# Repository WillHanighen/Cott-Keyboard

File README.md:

# Cott Keyboard
## A shitty 14-key MIDI keyboard

Idiot attempts PCB design n stuff for first time

## Hardware
 - [ESP32-S3-DevKitC-1-N32R16V](https://www.aliexpress.us/item/3256803793464226.html?gatewayAdapt=glo2usa) (note: URL dose not auto-select proper variant)
 - [Adafruit Monochrome 1.12" 128x128 OLED](https://www.adafruit.com/product/5297)
 - [STEMMA QT / Qwiic JST SH 4-Pin Cable](https://www.adafruit.com/product/4399)
 - [Analog 2-axis Thumb Joystick with Select Button + Breakout Board](https://www.adafruit.com/product/512)
 - [NeoPixel 5050 RGB LED with Integrated Driver Chip](https://www.adafruit.com/product/1655) (10 pack, buy 2; 14 total required)

### Power notice

This project was designed arround being powered by the DevKit's USB-C port, and the USB spec is max. 900mA for USB3, and 500mA for USB2 (what the type-c port communicates as)
In other words, keep the LED brightness down (~25% max, stinky I know, take it up with the USB implments fourm for not making it 2A, as [power that be] intended) and avoid whites.

## License

Licensed under CC BY-NC-SA 4.0: You can freely edit and redistribute this project as long as you credit me, don't do it commercially, and/or for monetary gain, and publish it under the same license.

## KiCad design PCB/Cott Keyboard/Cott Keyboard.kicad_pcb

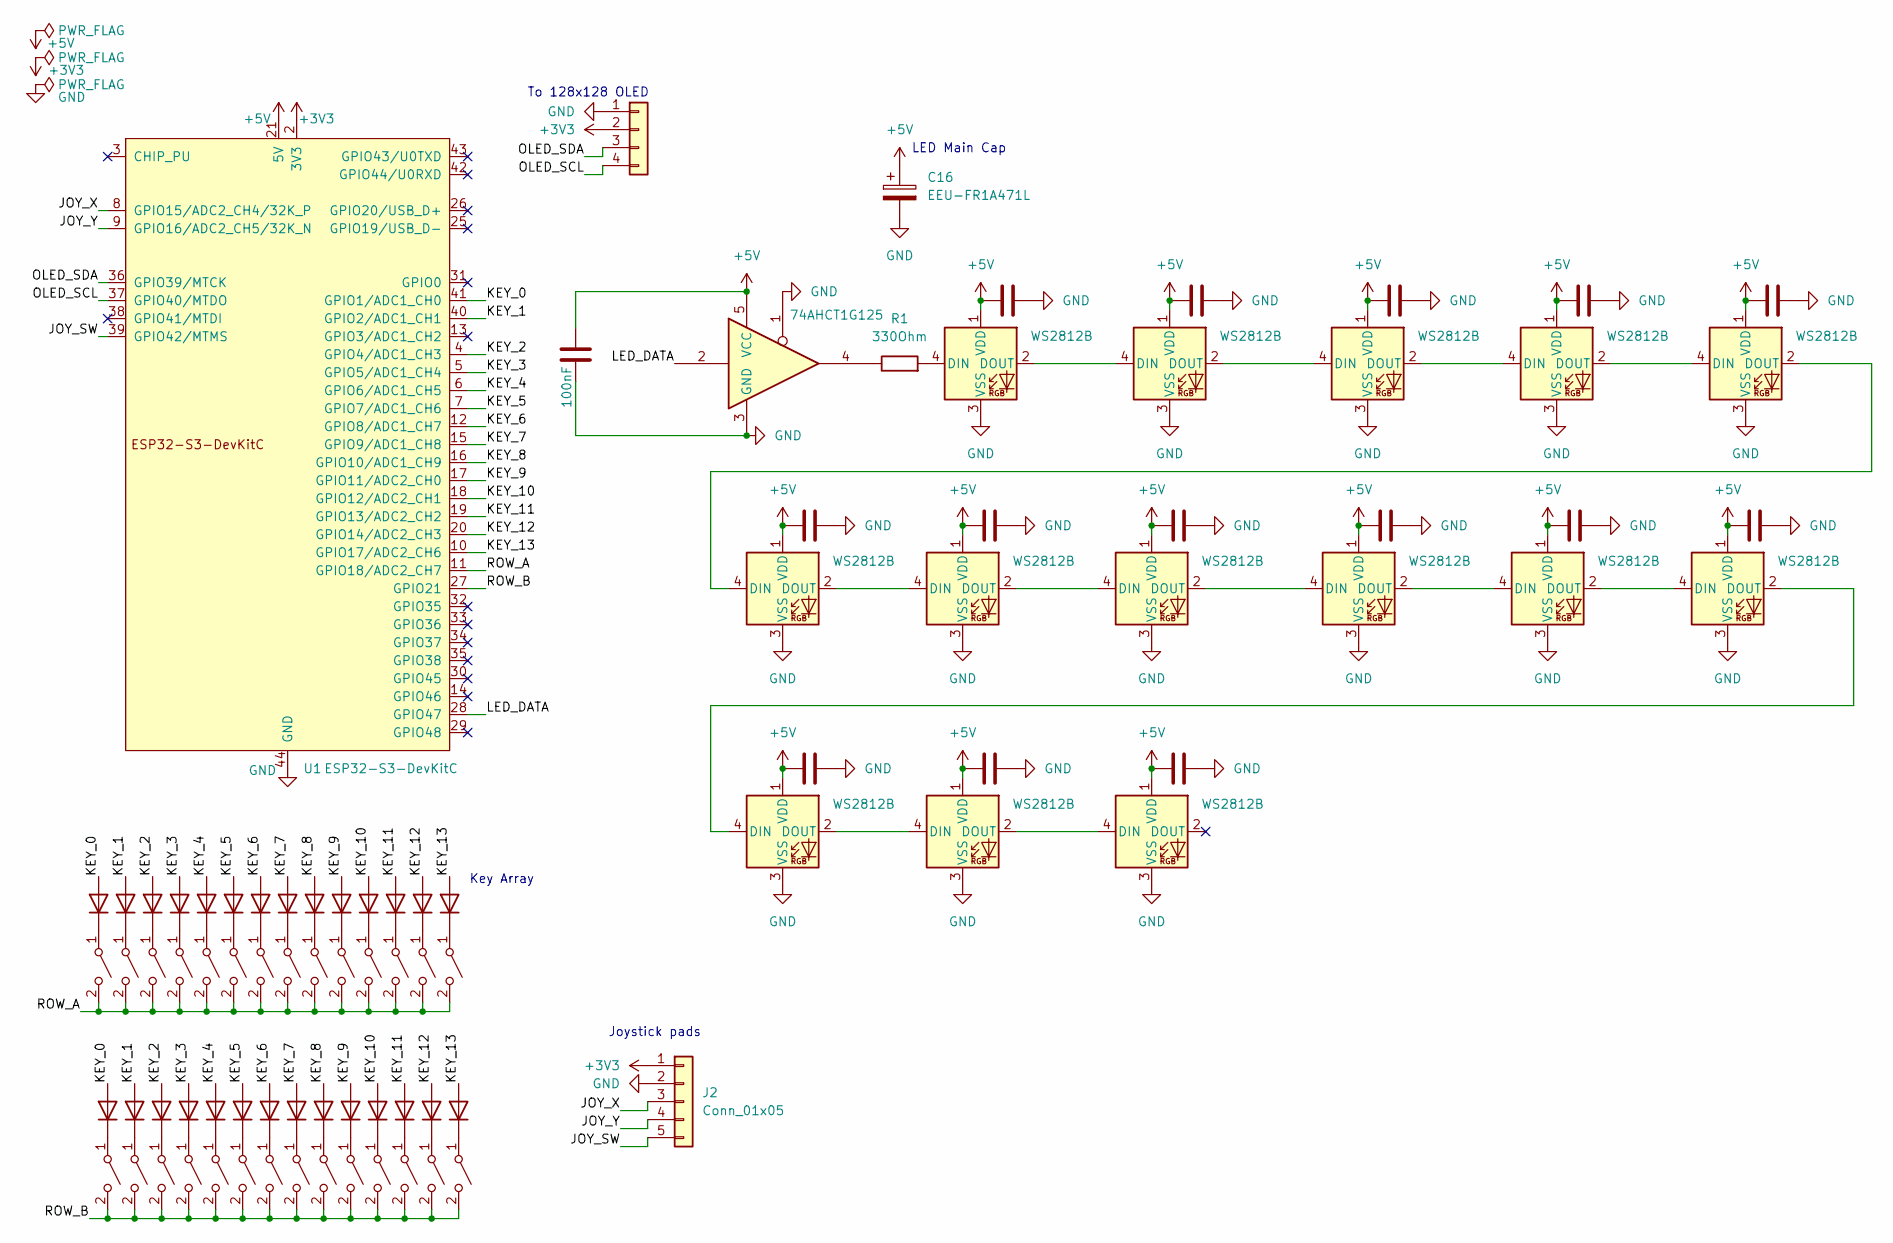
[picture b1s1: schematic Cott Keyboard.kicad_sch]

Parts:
C1, C2, C3, C4, C5, C6, C7, C8, C9, C10, C11, C12, C13, C14, C15: 100nF; C_0805_2012Metric_Pad1.18x1.45mm_HandSolder
C16: EEU-FR1A471L; CP_Radial_D8.0mm_P3.50mm
D1, D2, D3, D4, D5, D6, D7, D8, D9, D10, D11, D12, D13, D14, D15, D16, D17, D18, D19, D20, D21, D22, D23, D24, D25, D26, D27, D28: 1N4148W; D_SOD-123
D29, D30, D31, D32, D33, D34, D35, D36, D37, D38, D39, D40, D41, D42: WS2812B; LED_WS2812B_PLCC4_5.0x5.0mm_P3.2mm
J1: Conn_01x04; JST_SH_SM04B-SRSS-TB_1x04-1MP_P1.00mm_Horizontal
J2: Conn_01x05; SolderWire-0.25sqmm_1x05_P4.2mm_D0.65mm_OD1.7mm_Relief
R1: 330Ohm; R_0805_2012Metric_Pad1.20x1.40mm_HandSolder
SW1, SW2, SW3, SW4, SW5, SW6, SW7, SW8, SW9, SW10, SW11, SW12, SW13, SW14, SW15, SW16, SW17, SW18, SW19, SW20, SW21, SW22, SW23, SW24, SW25, SW26, SW27, SW28: D2F-01FL; SW_Omron_D2F-01FL_SPST_NO
U1: ESP32-S3-DevKitC
U2: 74AHCT1G125; SOT-23-5

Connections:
+3V3: J1.2, J2.1, U1.1 (3V3), U1.2 (3V3)
+5V: C1.1, C2.1, C3.1, C4.1, C5.1, C6.1, C7.1, C8.1, C9.1, C10.1, C11.1, C12.1, C13.1, C14.1, C15.2, C16.1, D29.1 (VDD), D30.1 (VDD), D31.1 (VDD), D32.1 (VDD), D33.1 (VDD), D34.1 (VDD), D35.1 (VDD), D36.1 (VDD), D37.1 (VDD), D38.1 (VDD), D39.1 (VDD), D40.1 (VDD), D41.1 (VDD), D42.1 (VDD), U1.21 (5V), U2.5 (VCC)
/JOY_SW: J2.5, U1.39 (GPIO42/MTMS)
/JOY_X: J2.3, U1.8 (GPIO15/ADC2_CH4/32K_P)
/JOY_Y: J2.4, U1.9 (GPIO16/ADC2_CH5/32K_N)
/KEY_0: D1.2 (A), D15.2 (A), U1.41 (GPIO1/ADC1_CH0)
/KEY_1: D2.2 (A), D16.2 (A), U1.40 (GPIO2/ADC1_CH1)
/KEY_2: D3.2 (A), D17.2 (A), U1.4 (GPIO4/ADC1_CH3)
/KEY_3: D4.2 (A), D18.2 (A), U1.5 (GPIO5/ADC1_CH4)
/KEY_4: D5.2 (A), D19.2 (A), U1.6 (GPIO6/ADC1_CH5)
/KEY_5: D6.2 (A), D20.2 (A), U1.7 (GPIO7/ADC1_CH6)
/KEY_6: D7.2 (A), D21.2 (A), U1.12 (GPIO8/ADC1_CH7)
/KEY_7: D8.2 (A), D22.2 (A), U1.15 (GPIO9/ADC1_CH8)
/KEY_8: D9.2 (A), D23.2 (A), U1.16 (GPIO10/ADC1_CH9)
/KEY_9: D10.2 (A), D24.2 (A), U1.17 (GPIO11/ADC2_CH0)
/KEY_10: D11.2 (A), D25.2 (A), U1.18 (GPIO12/ADC2_CH1)
/KEY_11: D12.2 (A), D26.2 (A), U1.19 (GPIO13/ADC2_CH2)
/KEY_12: D13.2 (A), D27.2 (A), U1.20 (GPIO14/ADC2_CH3)
/KEY_13: D14.2 (A), D28.2 (A), U1.10 (GPIO17/ADC2_CH6)
/LED_DATA: U1.28 (GPIO47), U2.2
/OLED_SCL: J1.4, U1.37 (GPIO40/MTDO)
/OLED_SDA: J1.3, U1.36 (GPIO39/MTCK)
/ROW_A: SW1.2 (B), SW2.2 (B), SW3.2 (B), SW4.2 (B), SW5.2 (B), SW6.2 (B), SW7.2 (B), SW8.2 (B), SW9.2 (B), SW10.2 (B), SW11.2 (B), SW12.2 (B), SW13.2 (B), SW14.2 (B), U1.11 (GPIO18/ADC2_CH7)
/ROW_B: SW15.2 (B), SW16.2 (B), SW17.2 (B), SW18.2 (B), SW19.2 (B), SW20.2 (B), SW21.2 (B), SW22.2 (B), SW23.2 (B), SW24.2 (B), SW25.2 (B), SW26.2 (B), SW27.2 (B), SW28.2 (B), U1.27 (GPIO21)
GND: C1.2, C2.2, C3.2, C4.2, C5.2, C6.2, C7.2, C8.2, C9.2, C10.2, C11.2, C12.2, C13.2, C14.2, C15.1, C16.2, D29.3 (VSS), D30.3 (VSS), D31.3 (VSS), D32.3 (VSS), D33.3 (VSS), D34.3 (VSS), D35.3 (VSS), D36.3 (VSS), D37.3 (VSS), D38.3 (VSS), D39.3 (VSS), D40.3 (VSS), D41.3 (VSS), D42.3 (VSS), J1.1, J2.2, U1.22 (GND), U1.23 (GND), U1.24 (GND), U1.44 (GND), U2.1, U2.3 (GND)
unnamed: D1.1 (K), SW1.1 (A)
unnamed: D2.1 (K), SW2.1 (A)
unnamed: D3.1 (K), SW3.1 (A)
unnamed: D4.1 (K), SW4.1 (A)
unnamed: D5.1 (K), SW5.1 (A)
unnamed: D6.1 (K), SW6.1 (A)
unnamed: D7.1 (K), SW7.1 (A)
unnamed: D8.1 (K), SW8.1 (A)
unnamed: D9.1 (K), SW9.1 (A)
unnamed: D10.1 (K), SW10.1 (A)
unnamed: D11.1 (K), SW11.1 (A)
unnamed: D12.1 (K), SW12.1 (A)
unnamed: D13.1 (K), SW13.1 (A)
unnamed: D14.1 (K), SW14.1 (A)
unnamed: D15.1 (K), SW15.1 (A)
unnamed: D16.1 (K), SW16.1 (A)
unnamed: D17.1 (K), SW17.1 (A)
unnamed: D18.1 (K), SW18.1 (A)
unnamed: D19.1 (K), SW19.1 (A)
unnamed: D20.1 (K), SW20.1 (A)
unnamed: D21.1 (K), SW21.1 (A)
unnamed: D22.1 (K), SW22.1 (A)
unnamed: D23.1 (K), SW23.1 (A)
unnamed: D24.1 (K), SW24.1 (A)
unnamed: D25.1 (K), SW25.1 (A)
unnamed: D26.1 (K), SW26.1 (A)
unnamed: D27.1 (K), SW27.1 (A)
unnamed: D28.1 (K), SW28.1 (A)
unnamed: D29.4 (DIN), R1.2
unnamed: D29.2 (DOUT), D30.4 (DIN)
unnamed: D30.2 (DOUT), D31.4 (DIN)
unnamed: D31.2 (DOUT), D32.4 (DIN)
unnamed: D32.2 (DOUT), D33.4 (DIN)
unnamed: D33.2 (DOUT), D34.4 (DIN)
unnamed: D34.2 (DOUT), D35.4 (DIN)
unnamed: D35.2 (DOUT), D36.4 (DIN)
unnamed: D36.2 (DOUT), D37.4 (DIN)
unnamed: D37.2 (DOUT), D38.4 (DIN)
unnamed: D38.2 (DOUT), D39.4 (DIN)
unnamed: D39.2 (DOUT), D40.4 (DIN)
unnamed: D40.2 (DOUT), D41.4 (DIN)
unnamed: D41.2 (DOUT), D42.4 (DIN)
unnamed: R1.1, U2.4

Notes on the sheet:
Key Array
To 128x128 OLED
LED Main Cap
Joystick pads

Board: 2 copper layers, 91 parts (0 on the bottom side), 68 nets, no tracks yet.
